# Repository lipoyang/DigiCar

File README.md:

# DigiCar (デジカー)

## 概要
DigiCarは[RumiCar](https://www.rumicar.com/ja/top-page/)互換のミニ四駆サイズの自動運転カーです。

DigiCarは[デジもく会](https://dezimoku.connpass.com/)が企画しています。

## コンセプト
- [DigiCarのコンセプト](document/DigiCar_concept1.png)
- [DigiCarの回路設計概略](document/DigiCar_concept2.png)

## ハードウェア

- [回路図 (PDF)](hard/DigiCar.pdf)
- [CADデータ (Eagle)](hard/)　(※アートワークは未着手)

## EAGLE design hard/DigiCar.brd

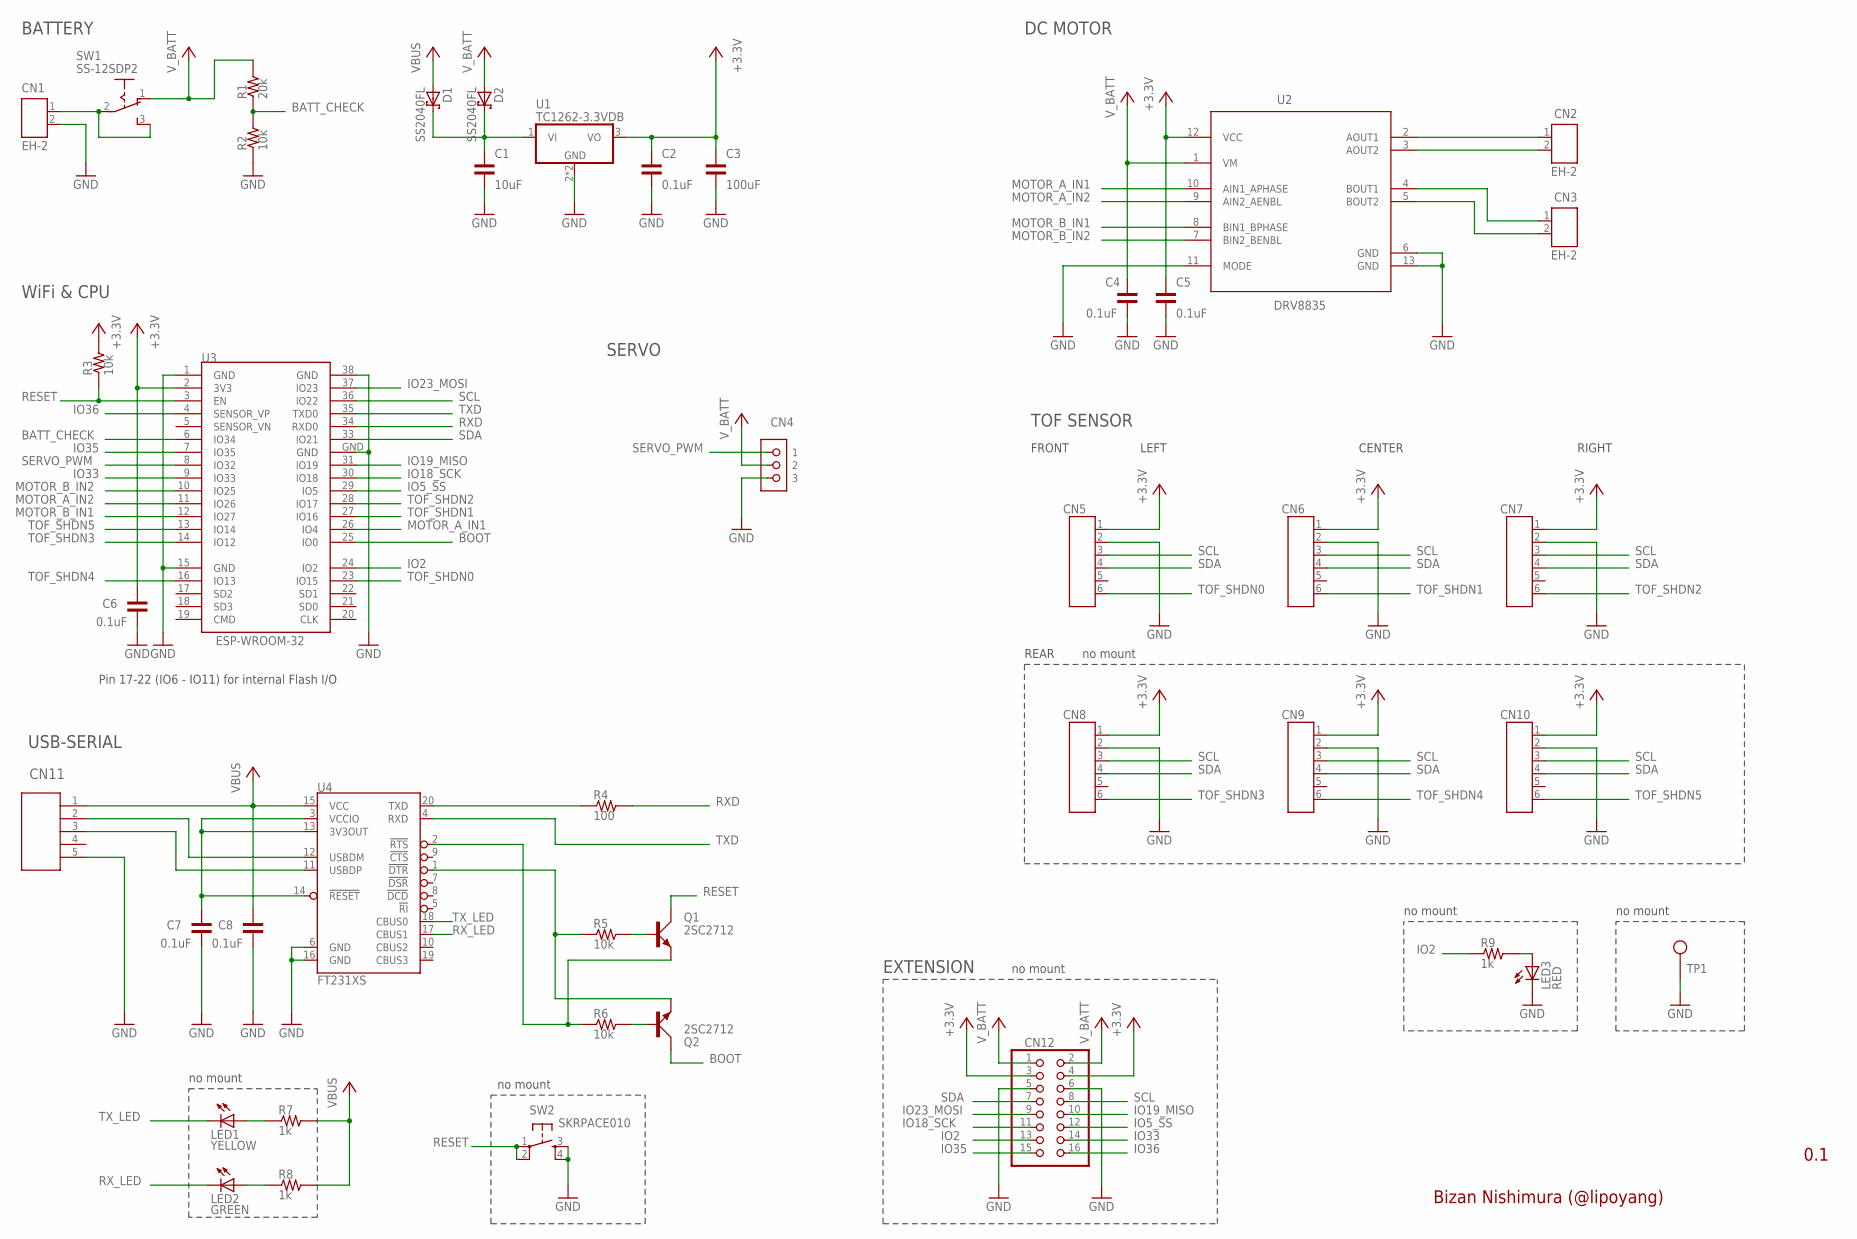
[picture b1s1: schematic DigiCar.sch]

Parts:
C1: 10uF; CP3216
C2, C4, C5, C6, C7, C8: 0.1uF; CP1608
C3: 100uF; CP3216
CN1, CN2, CN3: EH-2
CN4: PINHD-1X3; CON_RC_SERVO
CN5, CN6, CN7, CN8, CN9, CN10: PINHD-1X6; 1X06
CN11: ZX62-B-5PA(11); CONN_ZX62-B-5PA(11)_HIR
CN12: PINHD-2X8; 2X08
D1, D2: SS2040FL; SOD123
LED1: YELLOW; LED1608
LED2: GREEN; LED1608
LED3: RED; LED1608
Q1, Q2: 2SC2712; SC59
R1: 20k; CP1608
R2, R3, R5, R6: 10k; CP1608
R4: 100; CP1608
R7, R8, R9: 1k; CP1608
SW1: SS-12SDP2; SLIDE-SW
SW2: SKRPACE010
TP1: TEST_PIN
U1: TC1262-3.3VDB; SOT223
U2: DRV8835
U3: ESP-WROOM-32
U4: FT231XS; SSOP20

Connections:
+3V3: C2.SMD1 (PIN1), C3.SMD1 (PIN1), C5.SMD1 (PIN1), C6.SMD1 (PIN1), CN5.1, CN6.1, CN7.1, CN8.1, CN9.1, CN10.1, CN12.3, CN12.4, R3.SMD2 (PIN2), U1.3 (VO), U2.12 (VCC), U3.2 (3V3)
BATT_CHECK: R1.SMD1 (PIN1), R2.SMD2 (PIN2), U3.6 (IO34)
BOOT: Q2.C, U3.25 (IO0)
GND: C1.SMD2 (PIN2), C2.SMD2 (PIN2), C3.SMD2 (PIN2), C4.SMD2 (PIN2), C5.SMD2 (PIN2), C6.SMD2 (PIN2), C7.SMD2 (PIN2), C8.SMD2 (PIN2), CN1.2, CN4.3, CN5.2, CN6.2, CN7.2, CN8.2, CN9.2, CN10.2, CN11.5, CN12.5, CN12.6, LED3.C, R2.SMD1 (PIN1), SW2.3, SW2.4, TP1.1, U1.2 (GND), U1.4 (GND), U2.6 (GND), U2.11 (MODE), U2.13 (GND), U3.1 (GND), U3.15 (GND), U3.38 (GND), U3.GND, U4.6 (GND), U4.16 (GND)
IO2: CN12.13, R9.SMD1 (PIN1), U3.24 (IO2)
IO5_SS: CN12.12, U3.29 (IO5)
IO18_SCK: CN12.11, U3.30 (IO18)
IO19_MISO: CN12.10, U3.31 (IO19)
IO23_MOSI: CN12.9, U3.37 (IO23)
IO33: CN12.14, U3.9 (IO33)
IO35: CN12.15, U3.7 (IO35)
IO36: CN12.16, U3.4 (SENSOR_VP)
MOTOR_A_IN1: U2.10 (AIN1_APHASE), U3.26 (IO4)
MOTOR_A_IN2: U2.9 (AIN2_AENBL), U3.11 (IO26)
MOTOR_B_IN1: U2.8 (BIN1_BPHASE), U3.12 (IO27)
MOTOR_B_IN2: U2.7 (BIN2_BENBL), U3.10 (IO25)
unnamed: CN1.1, SW1.2, SW1.3 (S)
unnamed: LED3.A, R9.SMD2 (PIN2)
unnamed: C1.SMD1 (PIN1), D1.C, D2.C, U1.1 (VI)
unnamed: R4.SMD1 (PIN1), U4.20 (TXD)
unnamed: Q1.B, R5.SMD2 (PIN2)
unnamed: Q2.B, R6.SMD2 (PIN2)
unnamed: CN11.2, U4.12 (USBDM)
unnamed: CN11.3, U4.11 (USBDP)
unnamed: C7.SMD1 (PIN1), U4.3 (VCCIO), U4.13 (3V3OUT), U4.14 (!RESET)
unnamed: Q2.E, R5.SMD1 (PIN1), U4.1 (!DTR)
unnamed: Q1.E, R6.SMD1 (PIN1), U4.2 (!RTS)
unnamed: CN2.1, U2.2 (AOUT1)
unnamed: CN2.2, U2.3 (AOUT2)
unnamed: LED1.A, R7.SMD1 (PIN1)
unnamed: LED2.A, R8.SMD1 (PIN1)
unnamed: CN3.1, U2.4 (BOUT1)
unnamed: CN3.2, U2.5 (BOUT2)
RESET: Q1.C, R3.SMD1 (PIN1), SW2.1, SW2.2, U3.3 (EN)
RXD: R4.SMD2 (PIN2), U3.34 (RXD0)
RX_LED: LED2.C, U4.17 (CBUS1)
SCL: CN5.3, CN6.3, CN7.3, CN8.3, CN9.3, CN10.3, CN12.8, U3.36 (IO22)
SDA: CN5.4, CN6.4, CN7.4, CN8.4, CN9.4, CN10.4, CN12.7, U3.33 (IO21)
SERVO_PWM: CN4.1, U3.8 (IO32)
TOF_SHDN0: CN5.6, U3.23 (IO15)
TOF_SHDN1: CN6.6, U3.27 (IO16)
TOF_SHDN2: CN7.6, U3.28 (IO17)
TOF_SHDN3: CN8.6, U3.14 (IO12)
TOF_SHDN4: CN9.6, U3.16 (IO13)
TOF_SHDN5: CN10.6, U3.13 (IO14)
TXD: U3.35 (TXD0), U4.4 (RXD)
TX_LED: LED1.C, U4.18 (CBUS0)
VBUS: C8.SMD1 (PIN1), CN11.1, D1.A, R7.SMD2 (PIN2), R8.SMD2 (PIN2), U4.15 (VCC)
V_BATT: C4.SMD1 (PIN1), CN4.2, CN12.1, CN12.2, D2.A, R1.SMD2 (PIN2), SW1.1 (O), U2.1 (VM)

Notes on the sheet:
BATTERY
Bizan Nishimura (@lipoyang)
0.1
USB-SERIAL
DC MOTOR
WiFi & CPU
no mount
Pin 17-22 (IO6 - IO11) for internal Flash I/O
SERVO
TOF SENSOR
REAR
FRONT
LEFT
CENTER
RIGHT
EXTENSION

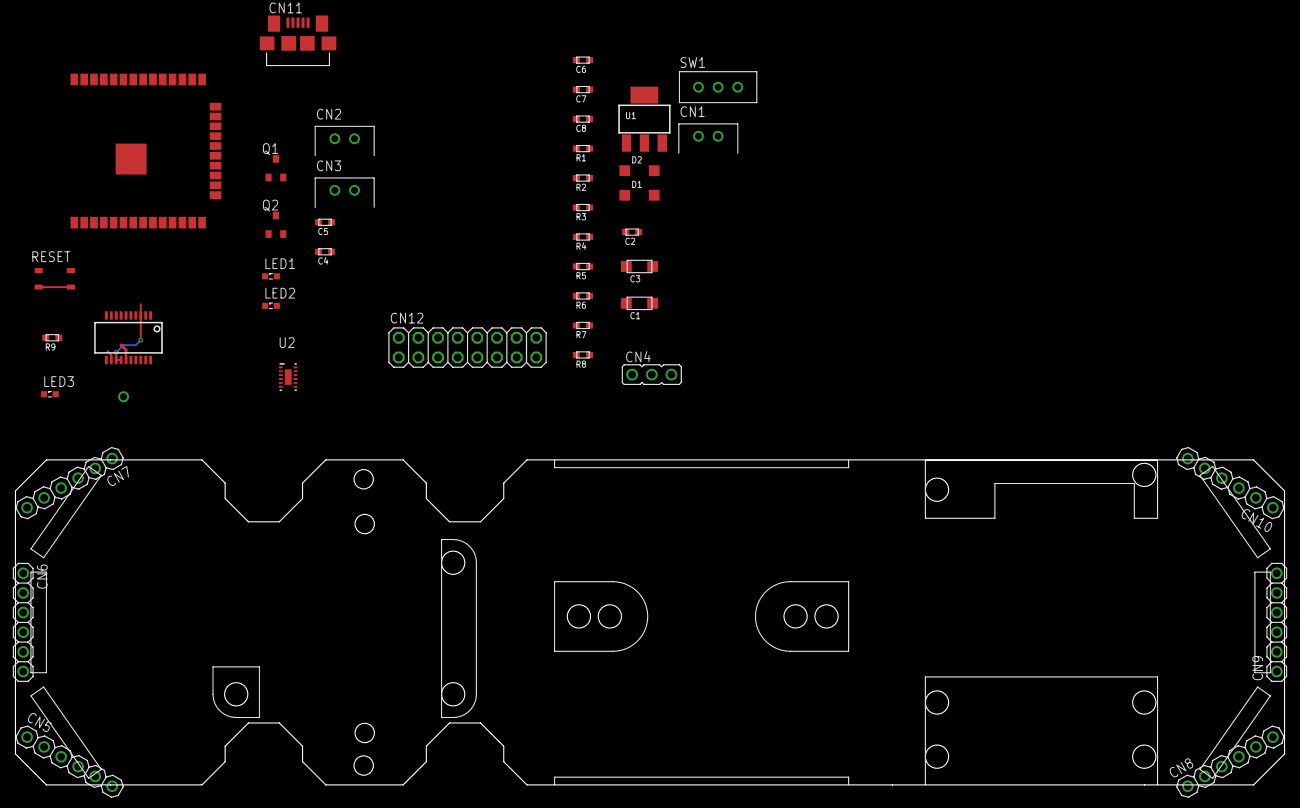
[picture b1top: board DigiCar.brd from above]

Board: 2 copper layers, 164.0 x 42.0 mm, 43 parts (0 on the bottom side), 49 nets.

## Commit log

2020-08-17 add readme
2020-08-17 modify README
2020-08-19 CADデータを追加
2020-08-19 READMEとCADデータを修正
2020-08-20 回路を修正
2020-09-01 基板外形データを追加
2020-09-01 .gitignoreを修正
2020-09-01 ボードに基板外形を作図
2020-09-01 基板外形を修正
2020-09-02 ToFセンサを配置(仮)

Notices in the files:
parts and their libraries:
COPYRIGHT: Copyright (C) 2018 Accelerated Designs. All rights reserved
lipoyang_frame: Released under the Creative Commons
Attribution Share-Alike 3.0 License
http://creativecommons.org/licenses/by-sa/3.0
